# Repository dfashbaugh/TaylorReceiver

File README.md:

# TaylorReceiver
This is the circuit board used for wireless lighting control in Taylor Swift's dress and her dancer's suits.

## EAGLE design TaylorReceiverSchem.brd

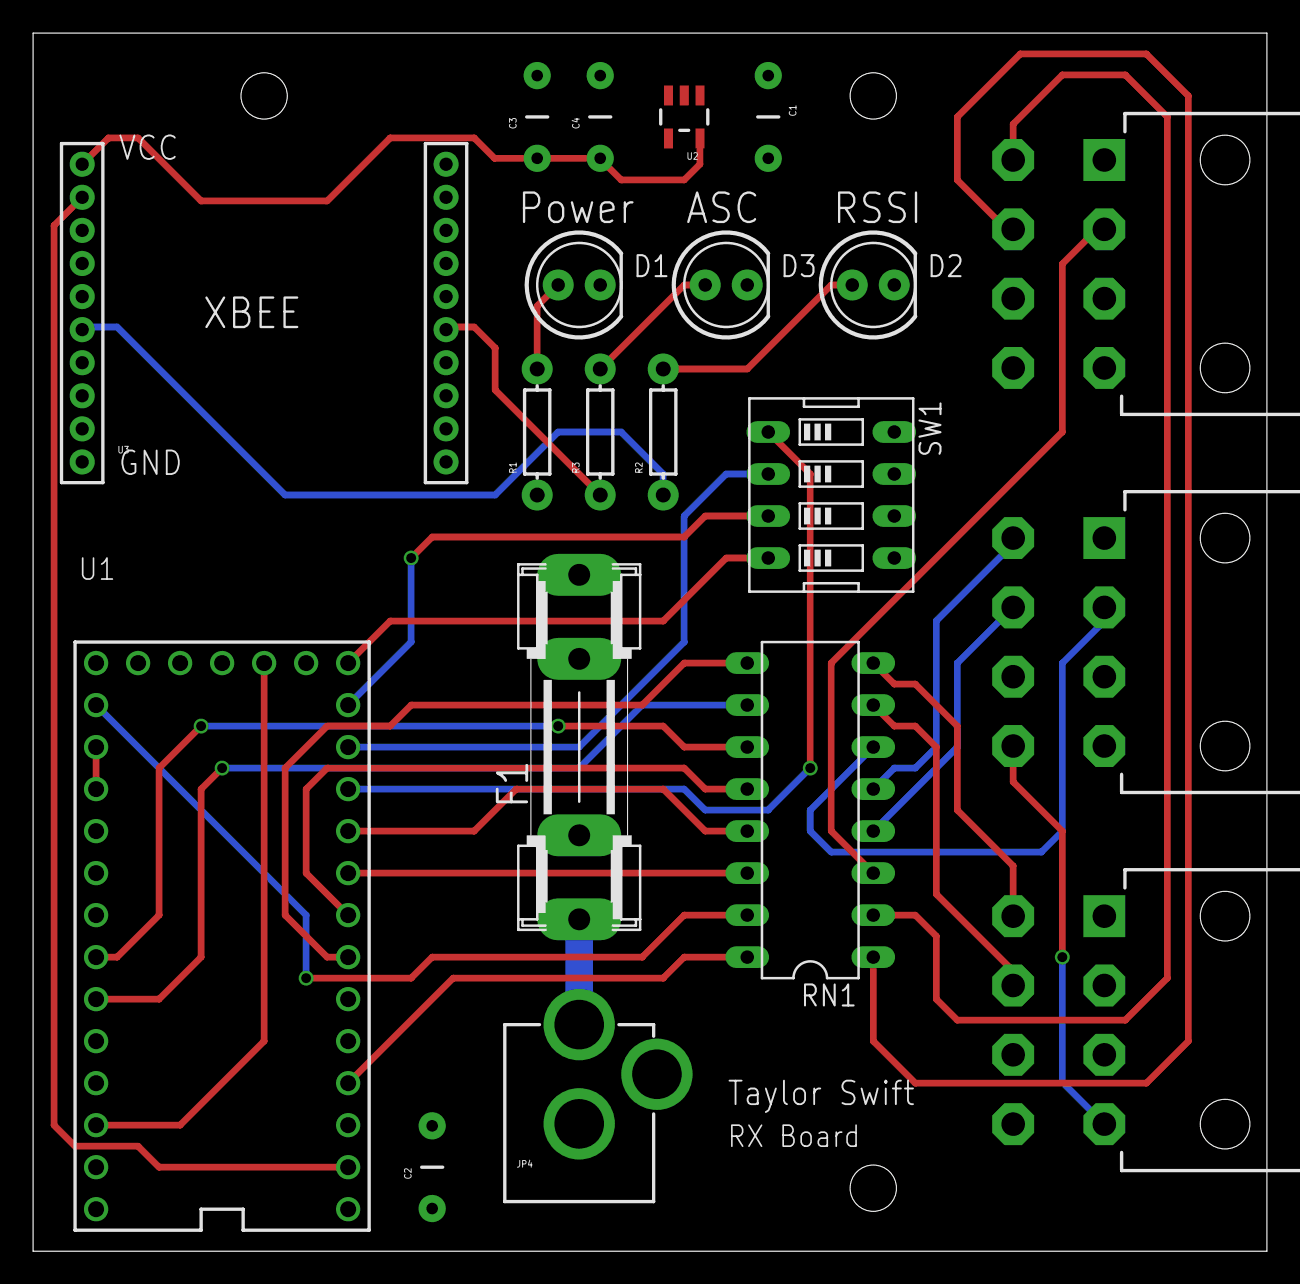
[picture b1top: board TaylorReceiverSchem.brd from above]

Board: 2 copper layers, 74.6 x 73.7 mm, 20 parts (0 on the bottom side), 32 nets.

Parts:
C1, C2, C3, C4: CAP-PTH-5MM
D1, D2, D3: LED5MM
F1: SHK20L
JP4: POWER_JACKPTH; POWER_JACK_PTH
P1, P2, P3: 39-30-08?_S; 39-30-?08?
R1, R2, R3: AXIAL-0.3
RN1: DIL16
SW1: EDG-04
U1: TEENSY_3.1_BASIC
U2: V_REG_LDOSMD; SOT23-5
U3: XBEE-1B1; XBEE-1

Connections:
3.3V: U1.3.3V, U1.3.3V1
ASC: R3.P$1, U3.15
DIP1: SW1.1, U1.9
DIP2: SW1.2, U1.10
DIP3: SW1.3, U1.11
DIP4: SW1.4, U1.12
GND: C1.2, C2.2, C3.2, C4.2, D1.K, D2.K, D3.K, JP4.GND, JP4.GNDBREAK, P1.3, P1.7, P2.3, P2.7, P3.3, P3.7, SW1.5, SW1.6, SW1.7, SW1.8, U1.GND, U1.GND1, U3.3, U3.10
unnamed: U1.15/A1, U1.16/A2
unnamed: F1.1A, JP4.PWR
unnamed: C3.1, C4.1, U2.5, U3.1
unnamed: P2.5, RN1.5
unnamed: P2.2, RN1.6
unnamed: P1.6, RN1.1
unnamed: P1.5, RN1.2
unnamed: P1.2, RN1.3
unnamed: P2.6, RN1.4
unnamed: P3.6, RN1.7
unnamed: P3.5, RN1.8
unnamed: D1.A, R1.P$2
unnamed: D2.A, R2.P$2
unnamed: D3.A, R3.P$2
RSSI: R2.P$1, U3.6
STRIP1: RN1.16, U1.2
STRIP2: RN1.15, U1.14/A0
STRIP3: RN1.14, U1.7
STRIP4: RN1.13, U1.8
STRIP5: RN1.12, U1.6
STRIP6: RN1.11, U1.20/A6
STRIP7: RN1.10, U1.21/A7
STRIP8: RN1.9, U1.5
VCC: C1.1, C2.1, F1.2A, P1.1, P1.4, P1.8, P2.1, P2.4, P2.8, P3.4, P3.8, R1.P$1, U1.VIN, U2.1, U2.3
XBEERECV: U1.0, U3.2

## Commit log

2015-05-10 Initial Commit of Taylor Swift RX Board Design
2015-05-10 Spelled Sheinkopf correctly.
2015-05-10 Improved PCB Routing
2015-06-03 New and improved board design
2015-06-06 Added right angle connectors to board.
2015-06-06 Added mounting holes.
2015-06-06 Moved the traces a safe distance from mounting holes.

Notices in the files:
parts and their libraries:
SparkFun-Capacitors: Licensing: Creative Commons ShareAlike 4.0 International - https://creativecommons.org/licenses/by-sa/4.0
con-molex-mini-fit: Copyright (C) 2011, Bob Starr
